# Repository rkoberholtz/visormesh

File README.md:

# VisorMesh

A MeshCore client for the Handspring Visor (Palm OS 3.5.2H3.0).

The Visor works as a terminal for a MeshCore **companion radio**. The radio (a Seeed XIAO nRF52840 with a Wio-SX1262) handles LoRa, routing and crypto. The Visor only speaks the companion framing protocol over a byte stream. The radio sits on a custom Springboard module with its own LiPo, so it keeps meshing while the Visor sleeps.

See [docs/design.md](docs/design.md) for the architecture and the reasons behind each decision, and [docs/progress.md](docs/progress.md) for the current status and log.

## Status

The Palm app works today over the Visor's USB cradle, through a bridge on a Mac to the radio's UART. The SB-LoRa module puts the radio in the Springboard slot instead. Its milestones:

1. **Palm app over USB:** conversations, channels, contacts, node settings and a map, running on a Visor Neo.
2. **Radio firmware:** MeshCore's companion firmware patched to also talk on the XIAO's D6/D7 UART.
3. **Rev 1 built:** boards made by JLCPCB (`hw-v0.1`). Its connector part went obsolete and the 1.6 mm board is too thick for the replacement, so it stays a test board.
4. **Rev 2 designed:** 4 layers, 0.8 mm, around the measured MCS-068SMA1 connector, with flash so the app loads when the module goes in. DRC clean.
5. **Rev 2 ordered** (in progress): fab files for JLCPCB and PCBWay, see [REV2.md](hardware/sb-lora/REV2.md#ordering-pcbway).
6. **Rev 2 assembled:** connector, XIAO, Wio and LiPo fitted by hand.
7. **Visor sees the module:** the slot reports the card and the flash ID reads back.
8. **App loads from the module's flash** on insertion.
9. **Radio over the slot:** a companion query round trip through the Springboard UART.
10. **Case and daily use:** the 3D-printed case fitted, and the module in everyday use.

The dated log is in [docs/progress.md](docs/progress.md).

## Screenshots

Taken on a Visor Neo (160 x 160, shown at 2x) on PhillyMesh.

| Home | Channel | Contacts | Repeater |
|---|---|---|---|
|  |  |  |  |

## SB-LoRa rev 2

| Top | Bottom | Case (draft) |
|---|---|---|
|  |  |  |

The XIAO and the Wio-SX1262 sit side by side at the outer end, outside the slot. In the slot: the S29AL008J flash (the module's app), the TL16C2550 UART and the level translators, with the connector straddling the board's inner edge. The LiPo is on the bottom, under the radios. Design notes are in [REV2.md](hardware/sb-lora/REV2.md).

## Repo layout

| Path | What |
|---|---|
| `hardware/sb-lora/` | SB-LoRa Springboard carrier board: KiCad, fab outputs (JLCPCB and PCBWay), generator scripts. See its [README](hardware/sb-lora/README.md) |
| `firmware/` | MeshCore companion firmware patch for the XIAO (UART on D6/D7 plus USB), build Makefile, bench query tool and a fake radio |
| `palm-client/` | VisorMesh, the Palm OS client: MeshTerm-style conversations, channels, contacts, node settings. Works over the Visor USB cradle via a Mac bridge until the SB-LoRa boards arrive. See its [README](palm-client/README.md) |
| `docs/design.md` | Architecture, protocol notes and decisions |
| `docs/progress.md` | Status, milestones and a dated log |
| `docs/upstream-issues.md` | Problems found in pilot-link, PilRC/prc-tools and MeshCore, with evidence and workarounds, ready to report |
| `docs/reference/` | Third-party reference: Handspring Springboard dev guide and mechanical spec, the Handspring SDK (`HsExt.h`, Springboard docs and tools), springSD v1.1 hardware |

## Versioning

Hardware revisions are tagged in git (`hw-v0.1`, `hw-v0.2`, ...), so the files that went to fab for each order stay recoverable. Each board's README records its revision and status.

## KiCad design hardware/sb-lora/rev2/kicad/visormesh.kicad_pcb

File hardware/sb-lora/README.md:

# VisorMesh SB-LoRa v0.1

A Springboard module for the Handspring Visor that carries a Seeed XIAO nRF52840 + Wio-SX1262 stack running MeshCore companion firmware. The Visor talks to it over a bit-banged SPI link into an SC16IS740 UART bridge. The XIAO runs from its own LiPo and keeps meshing while the Visor sleeps or the module is unplugged.

**Status: prototype design, not yet built.** DRC is clean (0 unconnected pads) and the netlist was cross-checked against the Springboard Development Guide pin table, the SC16IS740 datasheet pinout, and Dmitry Grinberg's springSD v1.1 connector footprint. Order 5 boards and build one before trusting it.

This README covers rev 1 (`hw-v0.1`). Rev 2 (flash, bus UART, XIAO and Wio side by side, 4 layers) is laid out in `rev2/`; see [REV2.md](REV2.md) for its status and what has to happen before it can be ordered.

## What's in here

| Path | What |
|---|---|
| `fab/visormesh_gerbers_jlcpcb.zip` | Gerbers + Excellon drill, upload as-is to JLCPCB or PCBWay |
| `fab/visormesh_bom_jlcpcb.csv` | BOM, JLC format (LCSC part numbers) |
| `fab/visormesh_cpl_jlcpcb.csv` | Pick-and-place, JLC format, top side only |
| `fab/hand_fit_parts.csv` | Parts you fit yourself (J1, J2, J3, JP1) |
| `fab/visormesh_schematic.pdf` | Net-label schematic + theory of operation |
| `fab/visormesh_assembly_top.pdf` | Assembly drawing with reference designators |
| `kicad/` | KiCad 7 board + project + custom DRC rule (opens in KiCad 7 or 8) |
| `source/` | The scripts that generated everything. `netlist.py` is the single source of truth |
| `../../firmware/` | MeshCore patch: `Xiao_nrf52_companion_radio_uart` env (companion protocol on D6/D7) |
| `renders/` | Top and bottom copper renders |

## Ordering (JLCPCB)

- PCB: 2 layers, **1.6 mm**, 1 oz, any color. **ENIG recommended** (flat pads for the 0.65 mm TSSOP, SC-70 parts and the straddle connector); lead-free HASL works too.
- Board is 50.43 x 75.15 mm. The bottom 50.47 mm is the in-slot section, using springSD's exact outline. The top 24.6 mm sticks out of the Visor and carries the XIAO stack.
- Assembly: top side, Economic PCBA is fine. Upload BOM + CPL. **Check part rotations in JLC's placement preview** before paying, especially U1-U7, Y1 and D1; KiCad and JLC disagree on rotation for some SOT/SC-70 footprints. Pin 1 of each IC is marked on the silkscreen and assembly drawing. The CPL already includes the corrections found in the first order's preview (U1, U2, U4 at 270; U3, U5-U7 at 180), so the dots should land on the pin-1 triangles without adjustment. Still glance at the preview: JLC can change its part models.
- Extended parts: SC16IS740 (C407851), 74LVC1G80 (C353857), crystal (C2901666) and probably the SN74LVC1T45 (C9382) and 74LVC1G04 (C10237). Expect extended-part loading fees.

## Parts you fit by hand

1. **J1 Springboard connector**: Hirose **IC1HA-68RD-1.27SH(51)**, the PC-Card-style straddle receptacle springSD uses. It clamps the board edge; pins 1-34 land on the top pads, 35-68 on the bottom.
   - **Obsolete** (no longer stocked at DigiKey or Mouser as of Nov 2026). Sources: new-old stock on eBay or brokers (search Octopart for the exact part number with the `(51)` suffix; about $24 each), or harvest one from a used Springboard module.
   - The Springboard connector core is a standard PCMCIA 68-pin connector with different housing keying (Dev Guide §5, §7.1). Handspring used four board-offset variants (−0.3, 0, +0.3, +0.6 mm); a harvested connector's offset sets how high the board sits in the slot, so compare it against a (51) or dry-fit before soldering.
   - An earlier note here suggested XKB X1321FV-2x34 (LCSC C2881777) as a substitute. That was never verified: the closest LCSC listing (X1321FVS-2x34, C2881881) is a vertical SMD socket, not an edge straddle, and won't fit this footprint.
   - Pin 1 is marked on silk at the right-hand end of the top row.
   - **Without the Hirose part.** The order for one was cancelled (Nov 2026). Rev 1 only uses these Springboard pins, so any receptacle that fits the slot needs about 12 good joints:

     | Signal | Pins |
     |---|---|
     | GND | 1, 34, 35, 68 |
     | CD1\*, CD2\* (to GND, or the OS sees no module) | 36, 67 |
     | VCC (VSB) | 17, 51 |
     | CS0\*, CS1\* | 7, 42 |
     | A8, A17 | 12, 46 |
     | D0 | 30 |
     | IRQ\* | 16 |
     | RESET\* | 58 |

     VDOCK (18, 52) is only needed if JP1 is bridged. Temporary options, best first:
     1. **Harvest a straddle connector** from a junk Springboard module (backup modules, Eyemodule, MiniJam and so on). It fits the footprint as designed; check its board offset against the slot first.
     2. **Donor connector on wires.** Cut a junk module's PCB just behind its connector, cut its traces, and wire its pads for the pins above to the matching J1 pads (or vias on the same nets). The donor strip sets the height in the slot; rev 1 sits outside, glued or taped to it.
     3. **Single-sided SMT PC Card receptacle** glued to the top at the edge. Top-row tails (1-34) go to the top pads where they line up (staggered tails need short jumpers). The 8 used bottom-row pins (35, 36, 42, 46, 51, 58, 67, 68) are wired around the edge to the bottom pads. The board then sits about 1 mm off the contact centre line, so dry-fit it: the edges may need filing to run in the slot's rails.
     4. **Receptacle from a junk PCMCIA card.** Same contacts, but its housing keys may block the Springboard slot, and a straddle part is sized for a thinner card PCB than 1.6 mm. Try it only if one is to hand.

     Whichever you use, check continuity from each used pin to its net and do the bench-power checks in [BRINGUP.md](BRINGUP.md) before it goes in the Visor.
2. **J2/J3**: two 1x7 2.54 mm female headers (low-profile if you can find them). Your XIAO+Wio stack plugs in here. You can also solder the stack's pins straight into the holes.
3. **JP1**: leave **open**. See VDOCK below.

## Mechanical / orientation

- The XIAO sits with **components facing up (same side as U1-U7) and USB-C at the outer edge**. Silkscreen labels (D0..D6, 5V, GND, 3V3, D10..D7) show which header pin goes where. **Check them against your stack before plugging in.** If your stack only exposes pins upside-down, the labels tell you it's mirrored.
- Solder your LiPo to the XIAO's BAT+/BAT- pads first. The carrier doesn't touch the battery; the XIAO's own charger handles it over USB-C.
- In-slot components are all 1.25 mm or shorter, on the top side only, which is lower than springSD's microSD socket. The bottom side inside the slot is a flat GND pour.
- **Assumption to verify:** like springSD, the top edge of the 50.47 mm section lines up with the slot opening, and the extension (with the stack and antenna) protrudes like a battery-module bump. Dry-fit a bare board before soldering anything.

## Electrical summary

- **Bus SPI** (same wiring as springSD, so its 68k routines port directly):
  - A CS0* access latches A17 and A8 on its rising edge. Through Q-bar, `nCS = NOT A17` and `MOSI = NOT A8`.
  - A CS1* read produces one SCLK pulse; MISO comes back on D0 through a 1k resistor.
  - SC16IS740 is SPI mode 0. Register byte: bit7 = R/W (1 = read), bits 6:3 = register, bits 2:1 = channel 00.
- **UART**: 14.7456 MHz crystal (SCTF SX3B14.7456F2010F30, 20 pF load; replaced the out-of-stock SXT32413BA07 rated 13 pF), so 115200 baud with DLL=8, DLH=0 (prescaler 1). 64-byte TX/RX FIFOs. IRQ* goes straight to the Springboard IRQ* (the Visor has the pull-up). RESET* follows the slot RESET*.
- **Power isolation**: only U5-U7 (SN74LVC1T45) touch both domains, and both of their ports go Hi-Z when either supply is 0 V. Removing the module, a LOWBAT power cut, or a flat LiPo can't back-power the other side.
- **Visor-present**: XIAO D0 is high when the slot is powered. The firmware can stop pushing frames when it's low; the companion queues messages anyway.
- **Slot budget**: a few mA active, against the 100 mA limit. To stay inside the 100 uA standby limit, put the SC16IS740 to sleep (IER bit 4) when the Palm app is idle.
- **VDOCK (JP1)**: when bridged, VDOCK (4.75-6.2 V, only present in a charging dock) feeds the XIAO 5V pin through a Schottky so the XIAO charger can top up the LiPo while docked. The standard Visor USB cradle almost certainly doesn't supply VDOCK on an AAA Visor. **If you bridge JP1, never plug USB-C in while docked**, because VDOCK would back-feed the USB host.

## Bring-up order

[BRINGUP.md](BRINGUP.md) has the full plan: checks and expected readings for each step, and what each line of the Visor's SB-LoRa Test means. In short:

1. Bare board, before soldering anything: check continuity of VSB (J1 pins 17/51) and GND, then dry-fit in the Visor slot.
2. After JLC assembly, fit J1 only. Bench-power VSB at 3.3 V through a current-limited supply. Expect a few mA, and the crystal at 14.7456 MHz on Y1.
3. Insert into the Visor with nothing on J2/J3. Port springSD's bus routines and read the SC16IS740 scratch register (SPR, reg 0x07): write and read back a pattern. That proves the CS0/CS1 latch path.
4. Flash the XIAO with `Xiao_nrf52_companion_radio_uart` (patch in `../../firmware/`). Bench-test it over a 3.3 V USB-TTL adapter on D6/D7 with meshcore-cli before plugging the stack into the carrier.
5. Plug in the stack. Configure the SC16IS740 for 115200 8N1, send CMD_DEVICE_QUERY (`<` + len + `0x16 0x03`), and look for a `>`-framed DEVICE_INFO reply.

## Known limits / things I could not verify from here

- Mechanical fit of the extension against the Visor body and the exact slot depth (see the assumption above).
- The J1 footprint is copied pad-for-pad from springSD v1.1 (verified against its IPC-356 netlist). I could not check it against the Hirose drawing.
- JLC part rotations (see Ordering).
- There is no `.kicad_sch`: the schematic is generated from `source/netlist.py` as a PDF, and the board's nets come from the same file. To regenerate on a machine with KiCad 7, Java and Freerouting 2.1: `source/make.sh` (autoroutes), then `make_fab.py`, `verify.py`, `draw_schematic.py`. Routing is nondeterministic between runs.

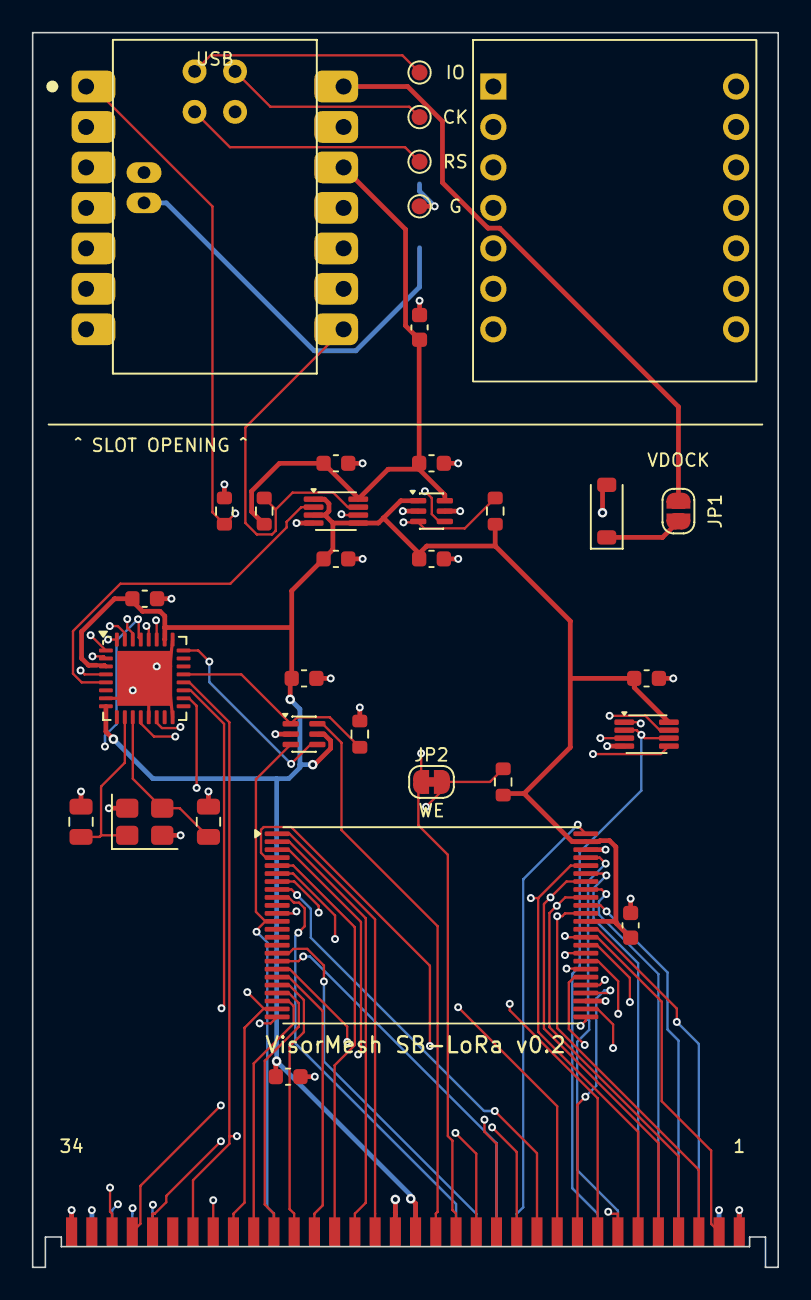
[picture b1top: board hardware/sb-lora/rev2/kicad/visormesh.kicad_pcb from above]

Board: 4 copper layers, 46.8 x 77.5 mm, 35 parts (1 on the bottom side), 72 nets.

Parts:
BT1: LiPo; BAT_PADS
C1, C12: 1uF; C_0603_1608Metric
C2, C3, C4, C5, C8, C9, C10, C11: 100nF; C_0603_1608Metric
C6, C7: 22pF C0G; C_0805_2012Metric
D1: B5819W; D_SOD-123
J1: MCS-068SMA1 straddle; SPRINGBOARD_68_STRADDLE
JP1: VDOCK EN; SolderJumper-2_P1.3mm_Open_RoundedPad1.0x1.5mm
JP2: FLASH WE; SolderJumper-2_P1.3mm_Bridged_RoundedPad1.0x1.5mm
R1, R2, R3, R5: 100k; R_0603_1608Metric
R4: 10k; R_0603_1608Metric
TP1: SWDIO; TestPoint_Pad_D1.0mm
TP2: SWCLK; TestPoint_Pad_D1.0mm
TP3: NRST; TestPoint_Pad_D1.0mm
TP4: GND; TestPoint_Pad_D1.0mm
U1: S29AL008J70TFI010; TSOP-I-48_18.4x12mm_P0.5mm
U2: TL16C2550RHBR; Texas_RHB0032E_VQFN-32-1EP_5x5mm_P0.5mm_EP3.45x3.45mm
U3: SN74LVC2G32DCUR; VSSOP-8_2.3x2mm_P0.5mm
U4: SN74LVC2G04DCKR; SOT-363_SC-70-6
U5: SN74LVC2T45DCUR; VSSOP-8_2.3x2mm_P0.5mm
U6: SN74LVC1T45DCKR; SOT-363_SC-70-6
X1: XIAO nRF52840; XIAO_SMD
X2: Wio-SX1262 for XIAO; WIO_PTH
Y1: 14.7456MHz 20pF; Crystal_SMD_3225-4Pin_3.2x2.5mm

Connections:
3V3X: C9.1, C11.1, C12.1, R1.1, U5.8, U6.6, X1.12, X2.12
A1: J1.28, U1.25, U2.20
A2: J1.27, U1.24, U2.19
A3: J1.26, U1.23, U2.18
A4: J1.25, U1.22
A5: J1.24, U1.21
A6: J1.23, U1.20
A7: J1.22, U1.19
A8: J1.12, U1.18
A9: J1.11, U1.8
A10: J1.8, U1.7
A11: J1.10, U1.6
A12: J1.21, U1.5
A13: J1.13, U1.4
A14: J1.14, U1.3
A15: J1.20, U1.2
A16: J1.19, U1.1
A17: J1.46, U1.48
A18: J1.47, U1.17
A19: J1.48, U1.16
A20: J1.49, U1.9
CS0_N: J1.7, U1.26
CS1_N: J1.42, U3.2, U3.6
D0: J1.30, U1.29, U2.27
D1: J1.31, U1.31, U2.28
D2: J1.32, U1.33, U2.29
D3: J1.2, U1.35, U2.30
D4: J1.3, U1.38, U2.31
D5: J1.4, U1.40, U2.32
D6: J1.5, U1.42, U2.1
D7: J1.6, U1.44, U2.2
D8: J1.64, U1.30
D9: J1.65, U1.32
D10: J1.66, U1.34
D11: J1.37, U1.36
D12: J1.38, U1.39
D13: J1.39, U1.41
D14: J1.40, U1.43
D15: J1.41, U1.45
GND: BT1.2, C1.2, C2.2, C3.2, C4.2, C5.2, C6.2, C7.2, C8.2, C9.2, C10.2, C11.2, C12.2, J1.1, J1.34, J1.35, J1.36, J1.67, J1.68, R3.2, R5.2, TP4.1, U1.27, U1.46, U2.7, U2.13, U2.16, U2.25, U2.33, U3.4, U4.2, U5.4, U6.2, U6.5, X1.13, X1.BAT-, X1.GND, X2.13, Y1.2, Y1.4
IRQ_N: J1.16, U4.6
LORA_BUSY: X1.4, X2.4
LORA_DIO1: X1.2, X2.2
LORA_MISO: X1.10, X2.10
LORA_MOSI: X1.11, X2.11
LORA_NSS: X1.5, X2.5
LORA_RESET: X1.3, X2.3
LORA_RXEN: X1.6, X2.6
LORA_SCK: X1.9, X2.9
NRST: TP3.1, X1.RST
OE_N: J1.9, U1.28, U3.1
RESET_N: J1.58, U1.12, U4.3
SWCLK: TP2.1, X1.SWCLK
SWDIO: TP1.1, X1.SWDIO
UART_INT: R5.1, U2.21, U4.1
UART_IOR_N: U2.14, U3.7
UART_IOW_N: U2.12, U3.3
UART_RESET: U2.24, U4.4
UART_RX: R2.2, U2.4, U6.3
UART_TX: U2.5, U5.2
VBAT: BT1.1, X1.BAT+
VDOCK: D1.2, J1.18, J1.52
VDOCK_D: D1.1, JP1.1
VISOR_PRESENT: R3.1, U5.6, X1.1
VSB: C1.1, C2.1, C3.1, C4.1, C5.1, C8.1, C10.1, J1.17, J1.51, R2.1, R4.1, U1.37, U1.47, U2.3, U2.8, U2.26, U3.8, U4.5, U5.1, U5.3, U5.5, U6.1
WE_FL_N: JP2.2, R4.2, U1.11
WE_N: J1.15, JP2.1, U3.5
XIAO_RX: R1.2, U5.7, X1.8
XIAO_TX: U6.4, X1.7
XIAO_VBUS: JP1.2, X1.14
XTAL1: C6.1, U2.10, Y1.1
XTAL2: C7.1, U2.11, Y1.3

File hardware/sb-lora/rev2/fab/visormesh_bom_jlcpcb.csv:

Comment,Designator,Footprint,LCSC Part #
1uF,"C1,C12",C_0603_1608Metric,C15849
100nF,"C2,C3,C4,C5,C8,C9,C10,C11",C_0603_1608Metric,C14663
22pF C0G,"C6,C7",C_0805_2012Metric,C24658
B5819W,D1,D_SOD-123,C8598
100k,"R1,R2,R3",R_0603_1608Metric,C25803
10k,R4,R_0603_1608Metric,C25804
S29AL016J70TFI020,U1,TSOP-I-48_18.4x12mm_P0.5mm,C914935
SC16C650BIBS,U2,HVQFN-32-1EP_5x5mm_P0.5mm_EP3.1x3.1mm,C729132
SN74LVC2G32DCUR,U3,VSSOP-8_2.3x2mm_P0.5mm,C91874
SN74LVC2G04DCKR,U4,SOT-363_SC-70-6,C105251
SN74LVC2T45DCUR,U5,VSSOP-8_2.3x2mm_P0.5mm,C15741
SN74LVC1T45DCKR,U6,SOT-363_SC-70-6,C9382
14.7456MHz 20pF,Y1,Crystal_SMD_3225-4Pin_3.2x2.5mm,C2901666

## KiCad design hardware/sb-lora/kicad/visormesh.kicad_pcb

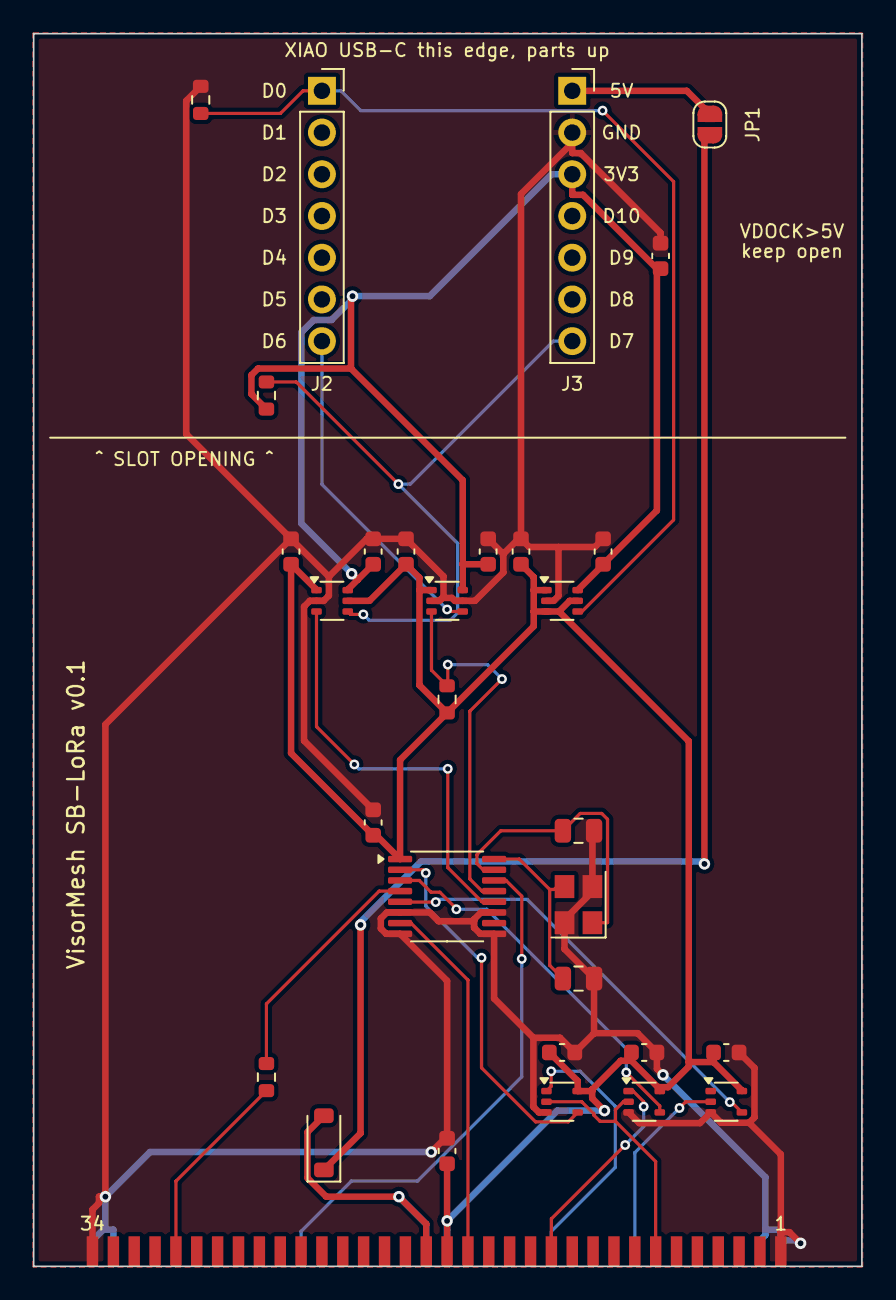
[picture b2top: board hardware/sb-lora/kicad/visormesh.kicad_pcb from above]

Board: 2 copper layers, 50.4 x 75.1 mm, 31 parts (0 on the bottom side), 24 nets.

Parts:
C1, C14: 1uF; C_0603_1608Metric
C2, C3, C4, C5, C8, C9, C10, C11, C12, C13: 100nF; C_0603_1608Metric
C6, C7: 22pF C0G; C_0805_2012Metric
D1: B5819W; D_SOD-123
J1: Springboard 68p; SPRINGBOARD_68_STRADDLE
J2: XIAO left 1x7; PinSocket_1x07_P2.54mm_Vertical
J3: XIAO right 1x7; PinSocket_1x07_P2.54mm_Vertical
JP1: VDOCK EN; SolderJumper-2_P1.3mm_Open_RoundedPad1.0x1.5mm
R1: 1k; R_0603_1608Metric
R2, R3, R4: 100k; R_0603_1608Metric
U1, U2: 74LVC1G80GW; SOT-353_SC-70-5
U3: 74LVC1G04GW; SOT-353_SC-70-5
U4: SC16IS740IPW; TSSOP-16_4.4x5mm_P0.65mm
U5, U6, U7: SN74LVC1T45DCKR; SOT-363_SC-70-6
Y1: 14.7456MHz 20pF; Crystal_SMD_3225-4Pin_3.2x2.5mm

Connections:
3V3X: C9.1, C11.1, C13.1, C14.1, J3.3, R2.1, U5.6, U6.6, U7.6
A8: J1.12, U2.1
A17: J1.46, U1.1
BR_RX: R3.2, U4.13, U6.3
BR_TX: U4.12, U5.3
CS0_N: J1.7, U1.2, U2.2
CS1_N: J1.42, U3.2
D0: J1.30, R1.1
GND: C1.2, C2.2, C3.2, C4.2, C5.2, C6.2, C7.2, C8.2, C9.2, C10.2, C11.2, C12.2, C13.2, C14.2, J1.1, J1.34, J1.35, J1.36, J1.67, J1.68, J3.2, R4.2, U1.3, U2.3, U3.3, U4.6, U4.8, U4.9, U4.11, U5.2, U6.2, U6.5, U7.2, Y1.2, Y1.4
IRQ_N: J1.16, U4.7
RESET_N: J1.58, U4.14
SPI_MISO: R1.2, U4.4
SPI_MOSI: U2.4, U4.3
SPI_NCS: U1.4, U4.2
SPI_SCLK: U3.4, U4.5
VDOCK: D1.2, J1.18, J1.52
VDOCK_D: D1.1, JP1.1
VISOR_PRESENT: J2.1, R4.1, U7.4
VSB: C1.1, C2.1, C3.1, C4.1, C5.1, C8.1, C10.1, C12.1, J1.17, J1.51, R3.1, U1.5, U2.5, U3.5, U4.1, U5.1, U5.5, U6.1, U7.1, U7.3, U7.5
XIAO_RX: J3.7, R2.2, U5.4
XIAO_TX: J2.7, U6.4
XIAO_VBUS: J3.1, JP1.2
XTAL1: C6.1, U4.15, Y1.1
XTAL2: C7.1, U4.16, Y1.3

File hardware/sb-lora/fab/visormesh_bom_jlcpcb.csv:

Comment,Designator,Footprint,LCSC Part #
1uF,"C1,C14",C_0603_1608Metric,C15849
100nF,"C2,C3,C4,C5,C8,C9,C10,C11,C12,C13",C_0603_1608Metric,C14663
22pF C0G,"C6,C7",C_0805_2012Metric,C24658
B5819W,D1,D_SOD-123,C8598
1k,R1,R_0603_1608Metric,C21190
100k,"R2,R3,R4",R_0603_1608Metric,C25803
74LVC1G80GW,"U1,U2",SOT-353_SC-70-5,C353857
74LVC1G04GW,U3,SOT-353_SC-70-5,C10237
SC16IS740IPW,U4,TSSOP-16_4.4x5mm_P0.65mm,C407851
SN74LVC1T45DCKR,"U5,U6,U7",SOT-363_SC-70-6,C9382
14.7456MHz 20pF,Y1,Crystal_SMD_3225-4Pin_3.2x2.5mm,C2901666
